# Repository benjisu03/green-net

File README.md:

# GreenNet
An IoT device for monitoring growing conditions in a greenhouse.

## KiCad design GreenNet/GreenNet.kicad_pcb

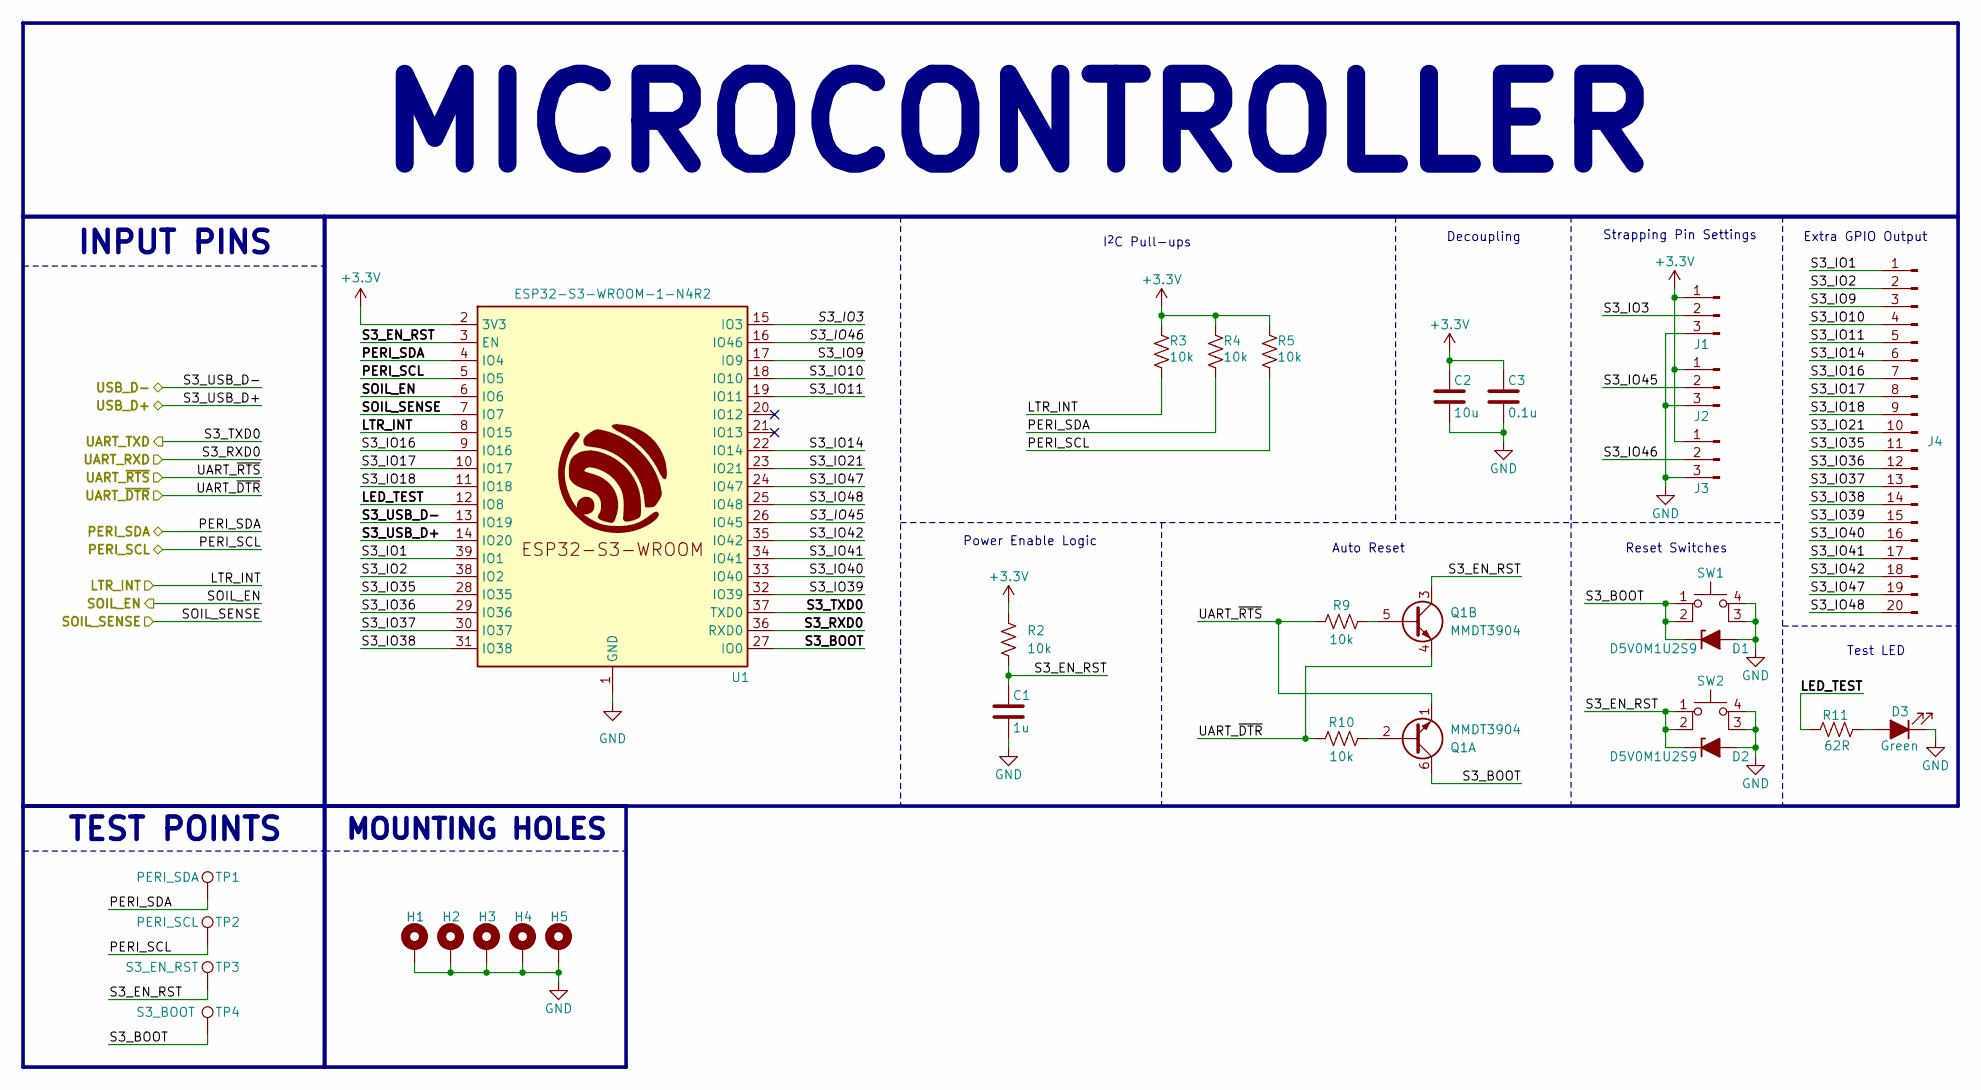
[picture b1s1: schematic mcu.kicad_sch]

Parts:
C1: 1u; C_0805_2012Metric
C2: 10u; C_0805_2012Metric
C3: 0.1u; C_0805_2012Metric
D1, D2: D5V0M1U2S9; D5V0M1U2S9Q
D3: Green; LED_0805_2012Metric
H1, H2, H3, H4, H5: MountingHole_Pad; MountingHole_2.5mm_Pad
J1, J2, J3: 3_Pin_Conn; 61300311121
J4: Conn_01x20_Pin; CONN_PH2-20-UA_ADM
Q1: MMDT3904; SOT-363_SC-70-6
R2, R3, R4, R5, R9, R10: 10k; R_0805_2012Metric
R11: 62R; R_0805_2012Metric
SW1, SW2: SW_MEC_5E; 18259106
TP1: PERI_SDA; RCWCTE
TP2: PERI_SCL; RCWCTE
TP3: S3_EN_RST; RCWCTE
TP4: S3_BOOT; RCWCTE
U1: ESP32-S3-WROOM-1-N4R2; ESP32S3WROOM1N16R2

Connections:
+3.3V: C2.1, C3.1, J1.1, J2.1, J3.1, R2.2, R3.2, R4.2, R5.2, U1.2 (3V3); also elsewhere on the board
/Input/LTR_INT: R3.1, U1.8 (IO15); also elsewhere on the board
/Input/PERI_SCL: R5.1, TP2.1, U1.5 (IO5); also elsewhere on the board
/Input/PERI_SDA: R4.1, TP1.1, U1.4 (IO4); also elsewhere on the board
/Input/SOIL_EN: U1.6 (IO6); also elsewhere on the board
/Input/SOIL_SENSE: U1.7 (IO7); also elsewhere on the board
/Input/UART_RXD: U1.37 (TXD0); also elsewhere on the board
/Input/UART_TXD: U1.36 (RXD0); also elsewhere on the board
/Input/UART_~DTR: Q1.4 (E2), R10.1; also elsewhere on the board
/Input/UART_~RTS: Q1.1 (E1), R9.1; also elsewhere on the board
/Input/USB_D+: U1.14 (IO20); also elsewhere on the board
/Input/USB_D-: U1.13 (IO19); also elsewhere on the board
/Microcontroller/LED_TEST: R11.1, U1.12 (IO8)
/Microcontroller/S3_BOOT: D1.1 (K), Q1.6 (C1), SW1.1, SW1.2, TP4.1, U1.27 (IO0)
/Microcontroller/S3_EN_RST: C1.1, D2.1 (K), Q1.3 (C2), R2.1, SW2.1, SW2.2, TP3.1, U1.3 (EN)
/Microcontroller/S3_IO1: J4.1, U1.39 (IO1)
/Microcontroller/S3_IO2: J4.2, U1.38 (IO2)
/Microcontroller/S3_IO3: J1.2, U1.15 (IO3)
/Microcontroller/S3_IO9: J4.3, U1.17 (IO9)
/Microcontroller/S3_IO10: J4.4, U1.18 (IO10)
/Microcontroller/S3_IO11: J4.5, U1.19 (IO11)
/Microcontroller/S3_IO14: J4.6, U1.22 (IO14)
/Microcontroller/S3_IO16: J4.7, U1.9 (IO16)
/Microcontroller/S3_IO17: J4.8, U1.10 (IO17)
/Microcontroller/S3_IO18: J4.9, U1.11 (IO18)
/Microcontroller/S3_IO21: J4.10, U1.23 (IO21)
/Microcontroller/S3_IO35: J4.11, U1.28 (IO35)
/Microcontroller/S3_IO36: J4.12, U1.29 (IO36)
/Microcontroller/S3_IO37: J4.13, U1.30 (IO37)
/Microcontroller/S3_IO38: J4.14, U1.31 (IO38)
/Microcontroller/S3_IO39: J4.15, U1.32 (IO39)
/Microcontroller/S3_IO40: J4.16, U1.33 (IO40)
/Microcontroller/S3_IO41: J4.17, U1.34 (IO41)
/Microcontroller/S3_IO42: J4.18, U1.35 (IO42)
/Microcontroller/S3_IO45: J2.2, U1.26 (IO45)
/Microcontroller/S3_IO46: J3.2, U1.16 (IO46)
/Microcontroller/S3_IO47: J4.19, U1.24 (IO47)
/Microcontroller/S3_IO48: J4.20, U1.25 (IO48)
GND: C1.2, C2.2, C3.2, D1.2 (A), D2.2 (A), D3.1 (K), H1.1, H2.1, H3.1, H4.1, H5.1, J1.3, J2.3, J3.3, SW1.3 (K), SW1.4 (A), SW2.3 (K), SW2.4 (A), U1.1 (GND), U1.40 (GND), U1.41 (EPAD), U1.42 (GND), U1.43 (GND), U1.44 (GND), U1.45 (GND), U1.46 (GND), U1.47 (GND), U1.48 (GND), U1.49 (GND); also elsewhere on the board
unnamed: D3.2 (A), R11.2
unnamed: Q1.2 (B1), R10.2
unnamed: Q1.5 (B2), R9.2

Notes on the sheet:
INPUT PINS
MOUNTING HOLES
MICROCONTROLLER
TEST POINTS
Test LED
Decoupling
Auto Reset
Extra GPIO Output
I^{2}C Pull-ups
Strapping Pin Settings
Reset Switches
Power Enable Logic

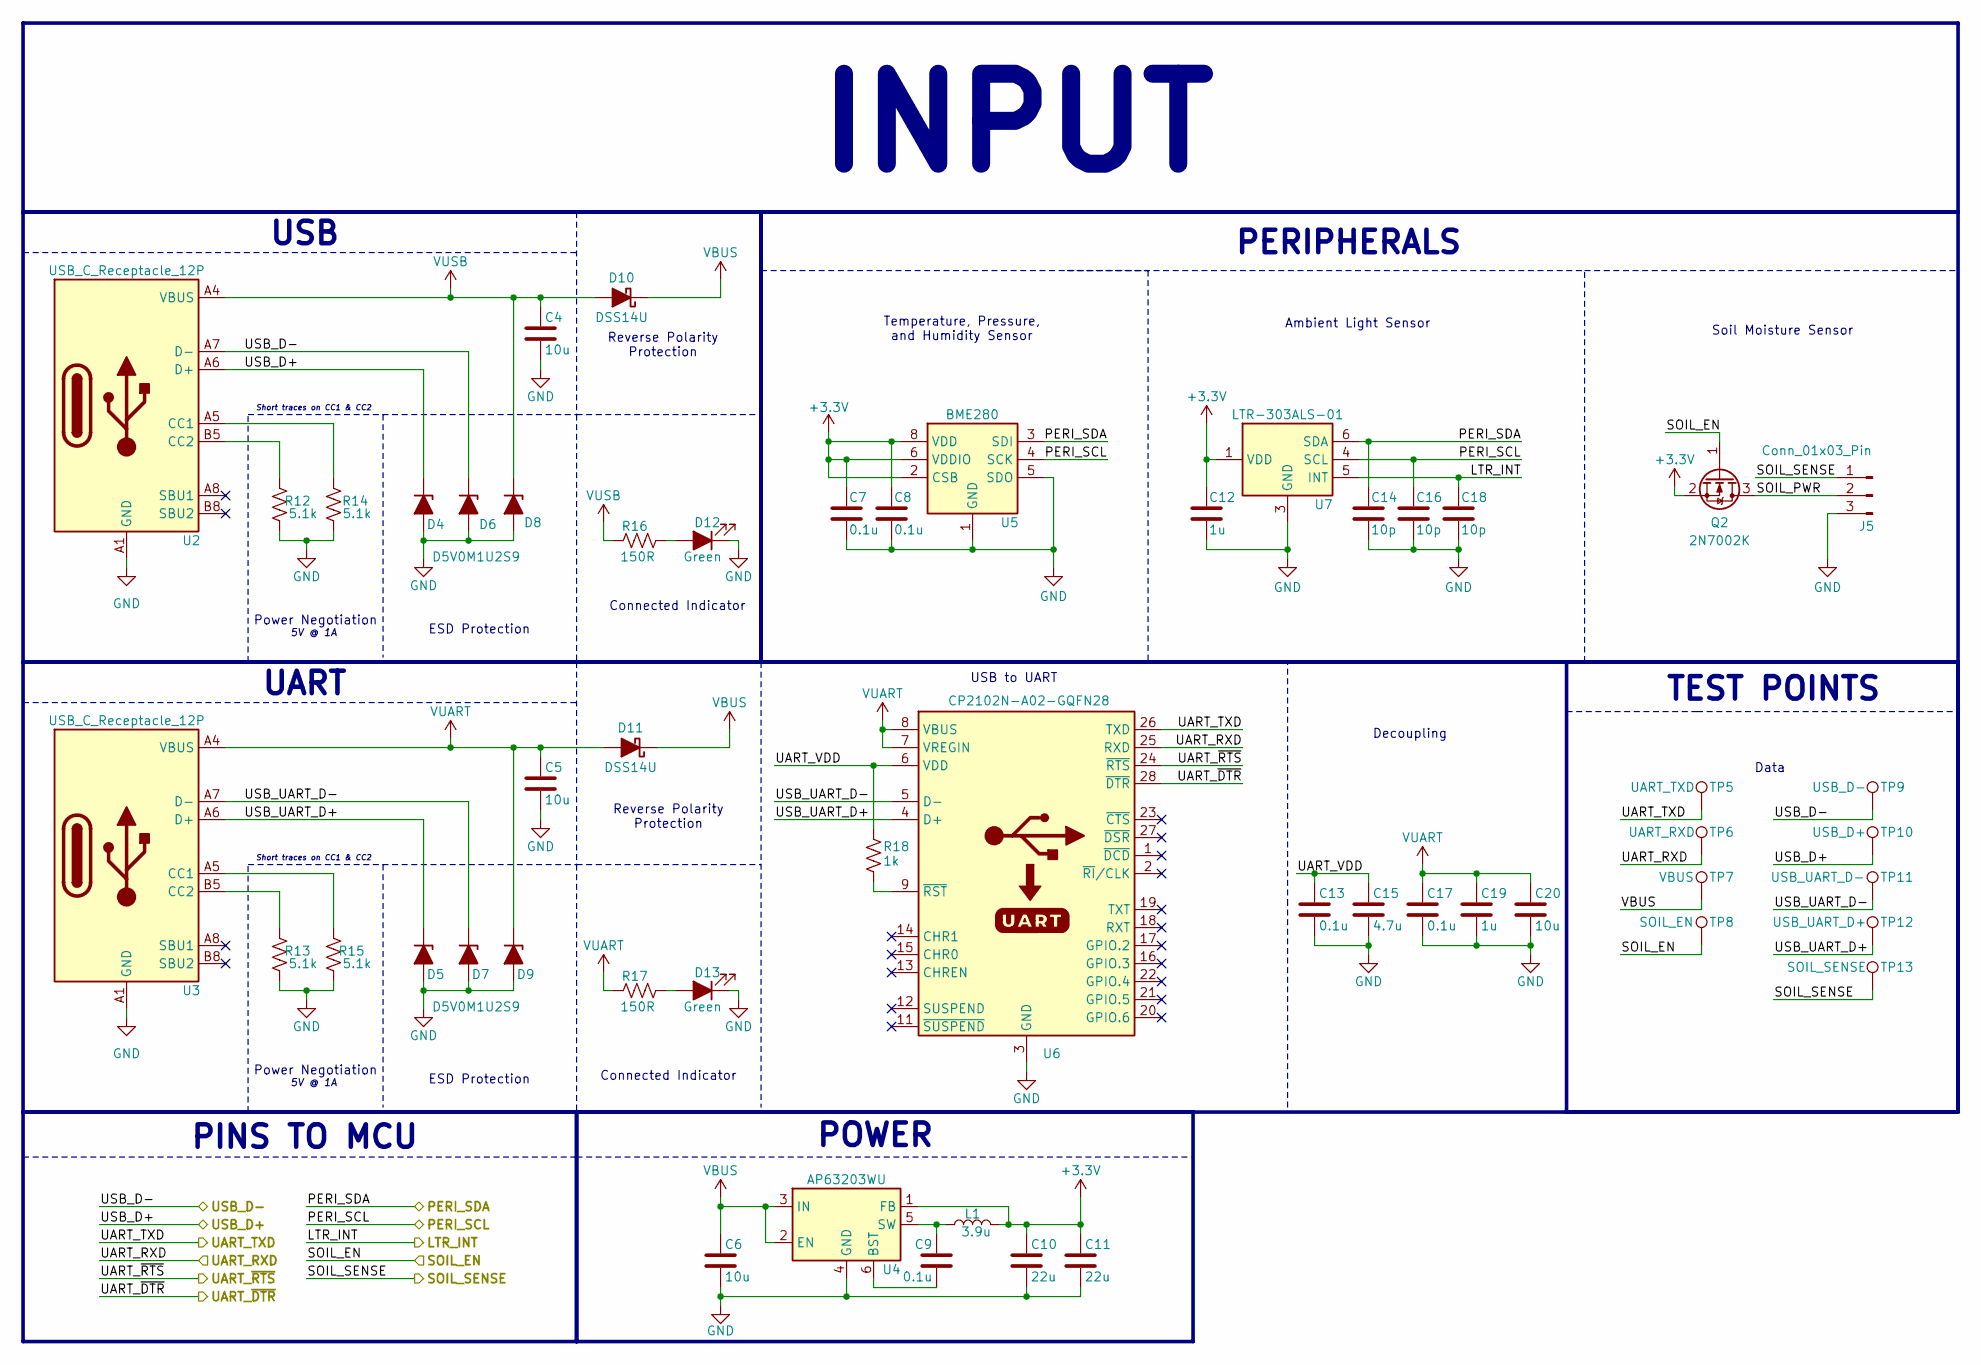
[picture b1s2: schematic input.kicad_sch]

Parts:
C4, C5, C6, C20: 10u; C_0805_2012Metric
C7, C8, C9, C13, C17: 0.1u; C_0805_2012Metric
C10, C11: 22u; C_0805_2012Metric
C12, C19: 1u; C_0805_2012Metric
C14, C16, C18: 10p; C_0805_2012Metric
C15: 4.7u; C_0805_2012Metric
D4, D5, D6, D7, D8, D9: D5V0M1U2S9; D5V0M1U2S9Q
D10, D11: DSS14U
D12, D13: Green; LED_0805_2012Metric
J5: Conn_01x03_Pin; 61300311121
L1: 3.9u; ASPI0628150MT1
Q2: 2N7002K; SOT-23
R12, R13, R14, R15: 5.1k; R_0805_2012Metric
R16, R17: 150R; R_0805_2012Metric
R18: 1k; R_0805_2012Metric
TP5: UART_TXD; RCWCTE
TP6: UART_RXD; RCWCTE
TP7: VBUS; RCWCTE
TP8: SOIL_EN; RCWCTE
TP9: USB_D-; RCWCTE
TP10: USB_D+; RCWCTE
TP11: USB_UART_D-; RCWCTE
TP12: USB_UART_D+; RCWCTE
TP13: SOIL_SENSE; RCWCTE
U2, U3: USB_C_Receptacle_12P; GCT_USB4105-GF-A
U4: AP63203WU; TSOT-23-6
U5: BME280; Bosch_LGA-8_2.5x2.5mm_P0.65mm_ClockwisePinNumbering
U6: CP2102N-A02-GQFN28; QFN-28-1EP_5x5mm_P0.5mm_EP3.35x3.35mm
U7: LTR-303ALS-01; Lite-On_LTR-303ALS-01

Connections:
+3.3V: C7.1, C8.1, C10.1, C11.1, C12.1, L1.2, Q2.2 (S), U4.1 (FB), U5.2 (CSB), U5.6 (VDDIO), U5.8 (VDD), U7.1 (VDD); also elsewhere on the board
/Input/LTR_INT: C18.1, U7.5 (INT); also elsewhere on the board
/Input/PERI_SCL: C16.1, U5.4 (SCK), U7.4 (SCL); also elsewhere on the board
/Input/PERI_SDA: C14.1, U5.3 (SDI), U7.6 (SDA); also elsewhere on the board
/Input/SOIL_EN: Q2.1 (G), TP8.1; also elsewhere on the board
/Input/SOIL_PWR: J5.2, Q2.3 (D)
/Input/SOIL_SENSE: J5.1, TP13.1; also elsewhere on the board
/Input/UART_RXD: TP6.1, U6.25 (RXD); also elsewhere on the board
/Input/UART_TXD: TP5.1, U6.26 (TXD); also elsewhere on the board
/Input/UART_VDD: C13.1, C15.1, R18.1, U6.6 (VDD)
/Input/UART_~DTR: U6.28 (~DTR); also elsewhere on the board
/Input/UART_~RTS: U6.24 (~RTS); also elsewhere on the board
/Input/USB_D+: D4.1 (K), TP10.1, U2.A6 (D+), U2.B6 (D+); also elsewhere on the board
/Input/USB_D-: D6.1 (K), TP9.1, U2.A7 (D-), U2.B7 (D-); also elsewhere on the board
/Input/USB_UART_D+: D5.1 (K), TP12.1, U3.A6 (D+), U3.B6 (D+), U6.4 (D+)
/Input/USB_UART_D-: D7.1 (K), TP11.1, U3.A7 (D-), U3.B7 (D-), U6.5 (D-)
GND: C4.2, C5.2, C6.2, C7.2, C8.2, C10.2, C11.2, C12.2, C13.2, C14.2, C15.2, C16.2, C17.2, C18.2, C19.2, C20.2, D4.2 (A), D5.2 (A), D6.2 (A), D7.2 (A), D8.2 (A), D9.2 (A), D12.1 (K), D13.1 (K), J5.3, R12.1, R13.1, R14.1, R15.1, U2.A1 (GND), U2.B1 (GND), U2.S1 (SHIELD), U3.A1 (GND), U3.B1 (GND), U3.S1 (SHIELD), U4.4 (GND), U5.1 (GND), U5.5 (SDO), U5.7 (GND), U6.3 (GND), U6.29 (GND), U7.3 (GND); also elsewhere on the board
unnamed: D12.2 (A), R16.2
unnamed: D13.2 (A), R17.2
unnamed: R14.2, U2.A5 (CC1)
unnamed: R12.2, U2.B5 (CC2)
unnamed: R15.2, U3.A5 (CC1)
unnamed: R13.2, U3.B5 (CC2)
unnamed: C9.2, U4.6 (BST)
unnamed: C9.1, L1.1, U4.5 (SW)
unnamed: R18.2, U6.9 (~RST)
VBUS: C6.1, D10.1 (K), D11.1 (K), TP7.1, U4.2 (EN), U4.3 (IN)
VUART: C5.1, C17.1, C19.1, C20.1, D9.1 (K), D11.2 (A), R17.1, U3.A4 (VBUS), U3.B4 (VBUS), U6.7 (VREGIN), U6.8 (VBUS)
VUSB: C4.1, D8.1 (K), D10.2 (A), R16.1, U2.A4 (VBUS), U2.B4 (VBUS)

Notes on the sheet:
Power Negotiation
Short traces on CC1 & CC2
INPUT
USB
Ambient Light Sensor
USB to UART
Connected Indicator
POWER
Reverse Polarity Protection
Decoupling
Soil Moisture Sensor
PERIPHERALS
5V @ 1A
TEST POINTS
ESD Protection
Data
Temperature, Pressure, and Humidity Sensor
PINS TO MCU
UART

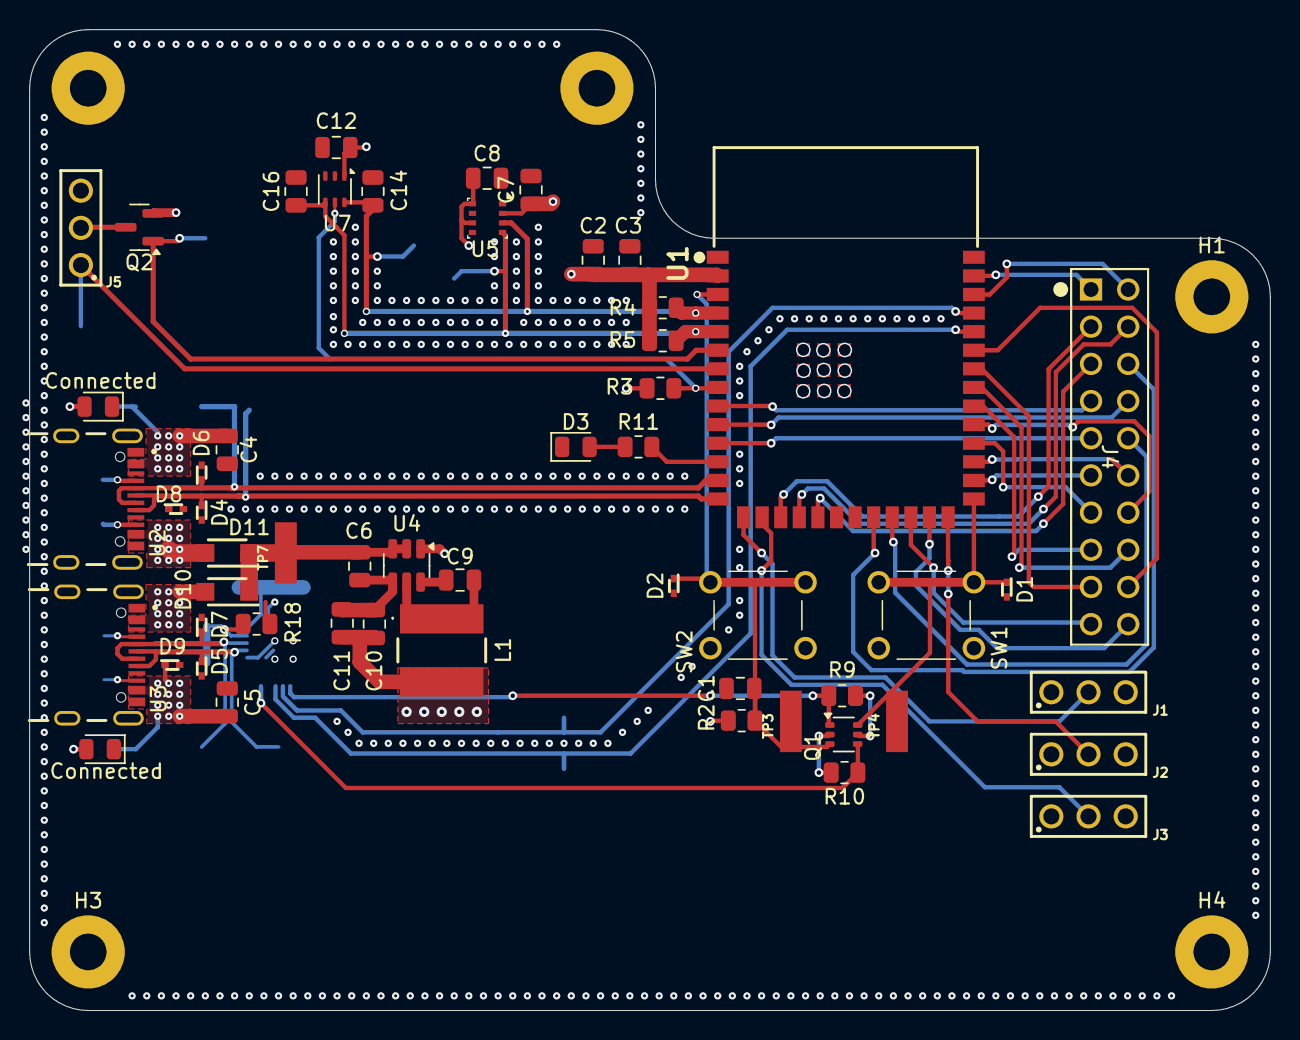
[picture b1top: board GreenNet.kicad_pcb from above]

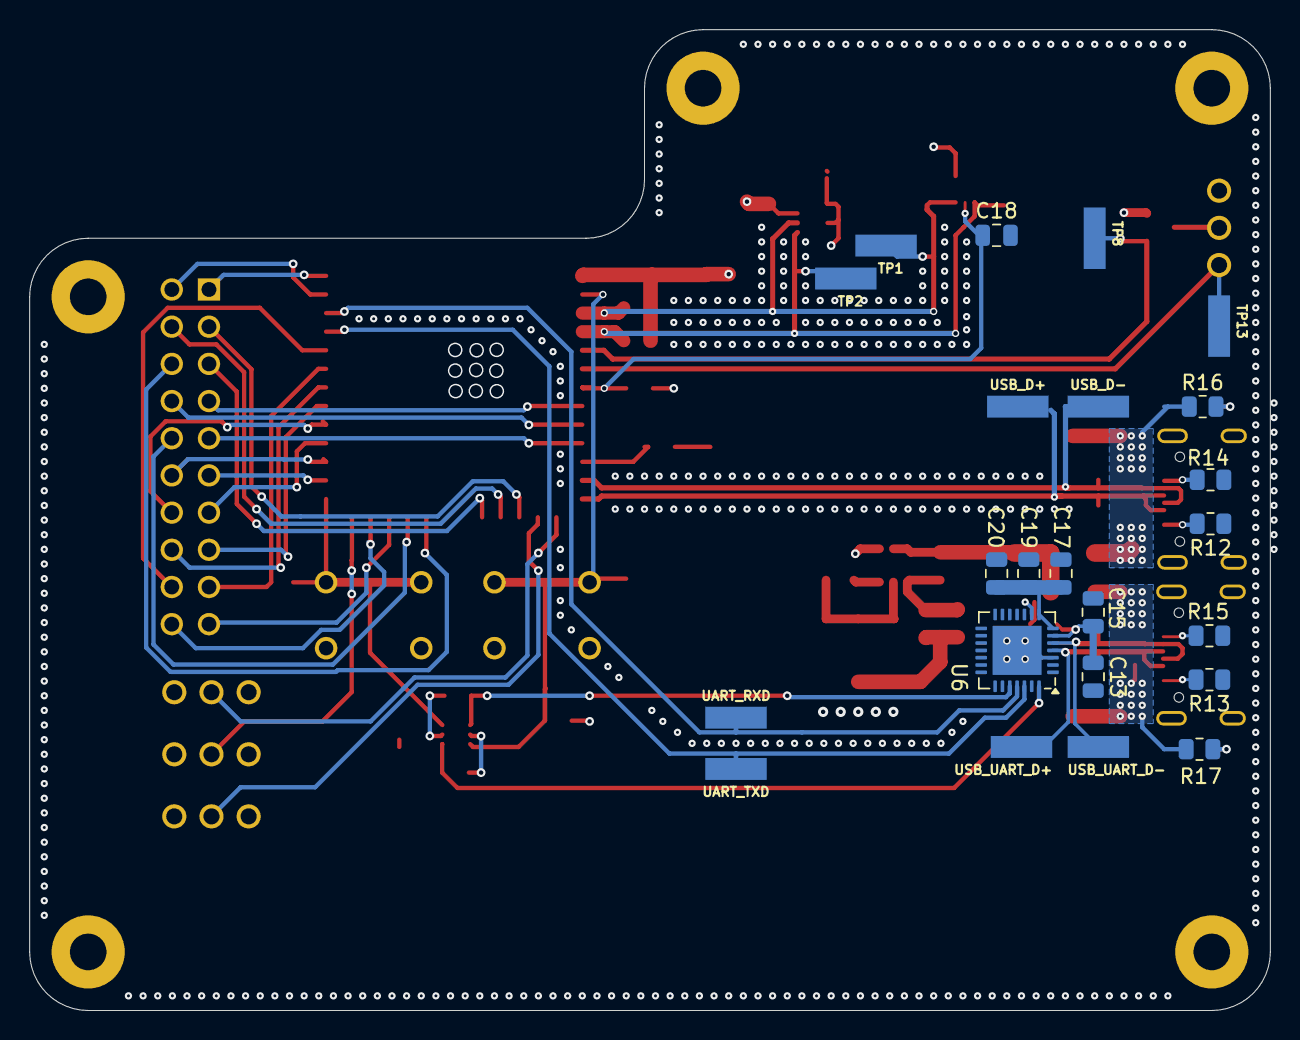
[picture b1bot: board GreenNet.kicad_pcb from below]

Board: 4 copper layers, 84.8 x 67.0 mm, 82 parts (23 on the bottom side), 58 nets.

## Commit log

2024-11-12 Create LICENSE
2024-11-13 intial update
2024-11-13 finished input schematic
2024-11-13 MCU fix
2024-11-14 USB-PC PD progress
2024-11-14 input schematic finished
2024-11-15 started layout
2024-11-16 more sensor work
2024-11-18 significant progress
2024-11-18 pre demo
2024-11-19 schematic FINAL
2024-11-20 layout update
